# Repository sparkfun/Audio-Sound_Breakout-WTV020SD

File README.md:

**NOTE:** *This product has been retired from our catalog. For alternatives, try looking at the following products from the [Audio boards](https://www.sparkfun.com/categories/343):*

* [Little Soundie Audio Player](https://www.sparkfun.com/products/14006)
* [Qwiic MP3 Trigger](https://www.sparkfun.com/products/15165)

*If you are looking for more up-to-date info, please check out some of these resources to see how other users are still hacking and improving on this product.*

* *[SparkFun Forum](https://forum.sparkfun.com/)*
* *[IRC Channel](https://www.sparkfun.com/news/263)*

Audio-Sound Breakout
====================

[  
*Audio-Sound Breakout (WIG-11125)*](https://www.sparkfun.com/products/11125)

* Firmware was compiled in Arduino 1.0.3.
* Hardware was developed in EAGLE 6.3.0.
* Fritzing part created under 0.7.12.

License Information
-------------------
The hardware design is released under [CC-SA v3 license](http://creativecommons.org/licenses/by-sa/3.0/us/).

The firmware is released under a modified beerware license, allowing for the purchase of any libation, alcoholic or non.

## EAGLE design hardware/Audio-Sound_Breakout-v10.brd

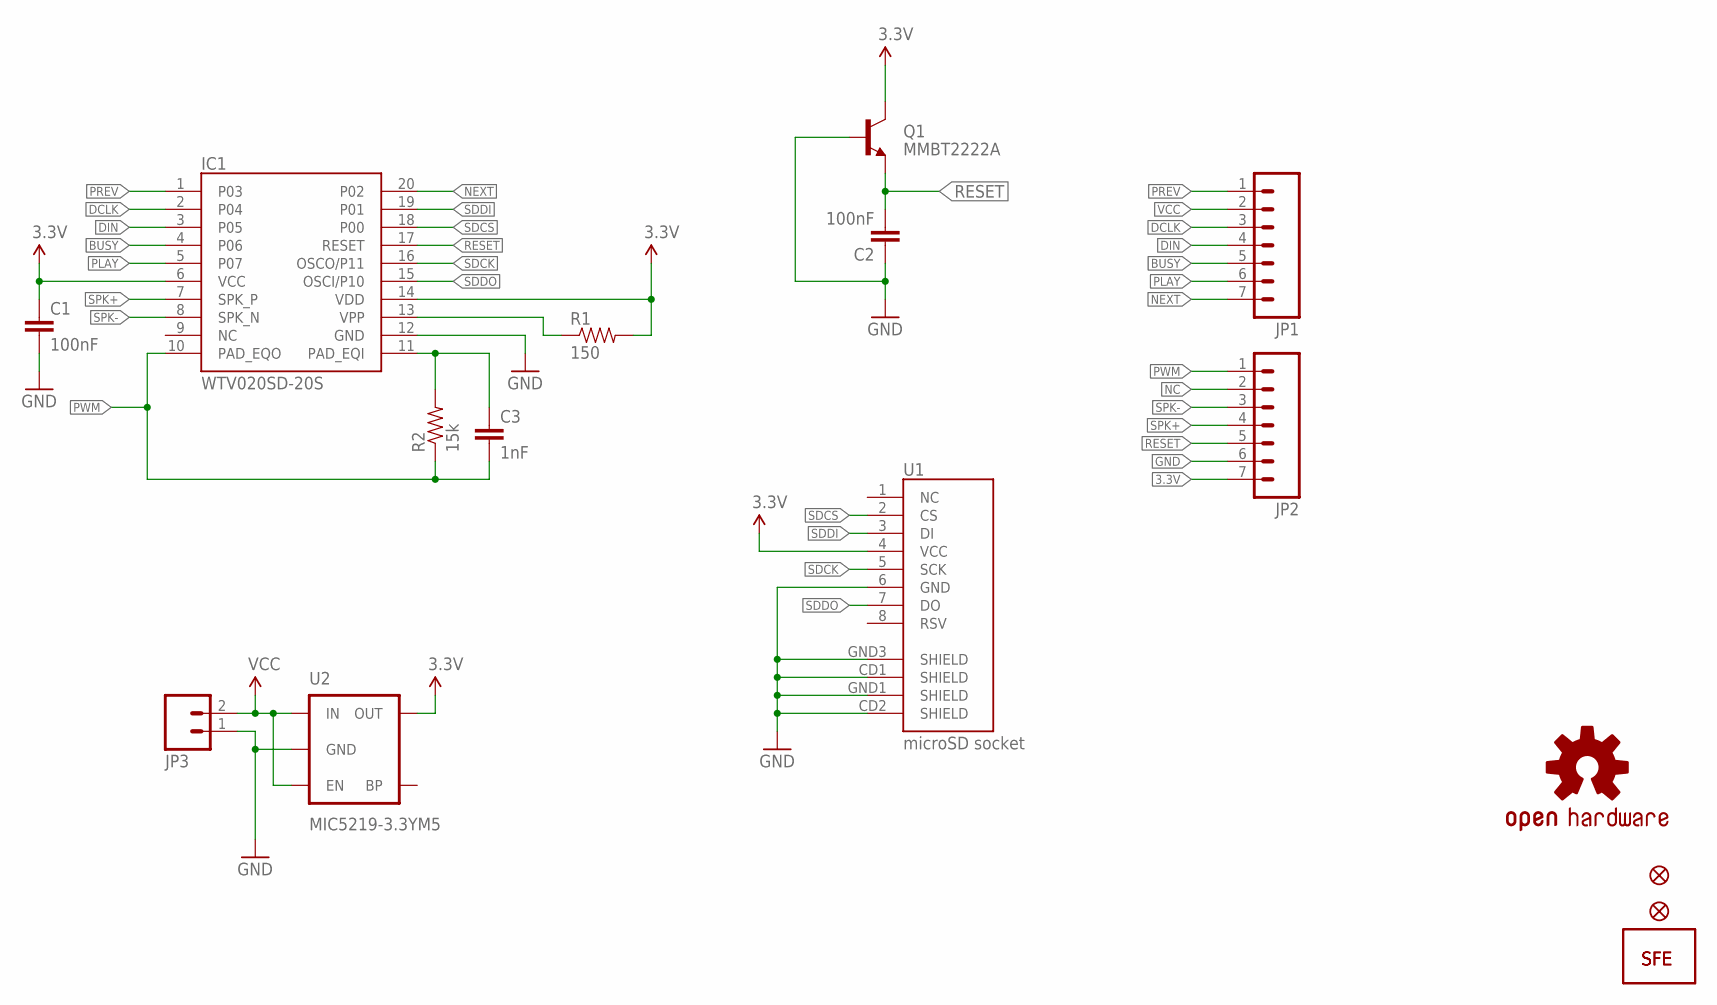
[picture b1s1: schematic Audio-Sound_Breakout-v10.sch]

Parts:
C1, C2: 100nF; 0402-CAP
C3: 1nF; 0402-CAP
IC1: WTV020SD-20S; SSOP_20
JP1, JP2: M07; 1X07
JP3: M02-JST-2MM-SMT; JST-2-SMD
JP4: LOGO-SFENW2; SFE-NEW-WEB
JP5: LOGO-SFENEW; SFE-NEW-WEBLOGO
JP6, JP7: FIDUCIALUFIDUCIAL; MICRO-FIDUCIAL
Q1: MMBT2222A; SOT23
R1: 150; 0402-RES
R2: 15k; 0402-RES
U1: microSD socket; MICRO-SD-SOCKET-PP
U2: MIC5219-3.3YM5; SOT23-5
U$1: OSHW-LOGOS; OSHW-LOGO-S

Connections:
3.3V: C1.1, IC1.6 (VCC), IC1.14 (VDD), JP2.7, Q1.3 (C), R1.2, U1.4 (VCC), U2.5 (OUT)
BUSY: IC1.4 (P06), JP1.5
DCLK: IC1.2 (P04), JP1.3
DIN: IC1.3 (P05), JP1.4
GND: C1.2, C2.1, IC1.12 (GND), JP2.6, JP3.1 (2), Q1.1 (B), U1.6 (GND), U1.CD1 (SHIELD), U1.CD2 (SHIELD), U1.GND1 (SHIELD), U1.GND3 (SHIELD), U2.2 (GND)
unnamed: IC1.13 (VPP), R1.1
unnamed: C3.1, IC1.11 (PAD_EQI), R2.2
NC: JP2.2
NEXT: IC1.20 (P02), JP1.7
PLAY: IC1.5 (P07), JP1.6
PREV: IC1.1 (P03), JP1.1
PWM: C3.2, IC1.10 (PAD_EQO), JP2.1, R2.1
RESET: C2.2, IC1.17 (RESET), JP2.5, Q1.2 (E)
SDCK: IC1.16 (OSCO/P11), U1.5 (SCK)
SDCS: IC1.18 (P00), U1.2 (CS)
SDDI: IC1.19 (P01), U1.3 (DI)
SDDO: IC1.15 (OSCI/P10), U1.7 (DO)
SPK+: IC1.7 (SPK_P), JP2.4
SPK-: IC1.8 (SPK_N), JP2.3
VCC: JP1.2, JP3.2 (1), U2.1 (IN), U2.3 (EN)

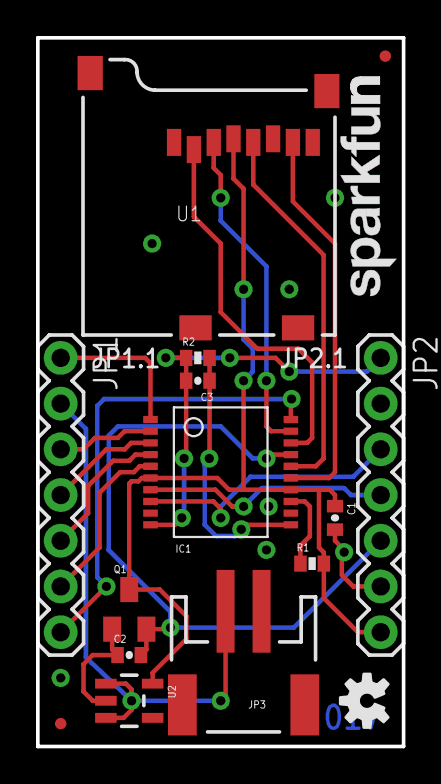
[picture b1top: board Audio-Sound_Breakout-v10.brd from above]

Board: 2 copper layers, 20.3 x 39.4 mm, 17 parts (1 on the bottom side), 19 nets.

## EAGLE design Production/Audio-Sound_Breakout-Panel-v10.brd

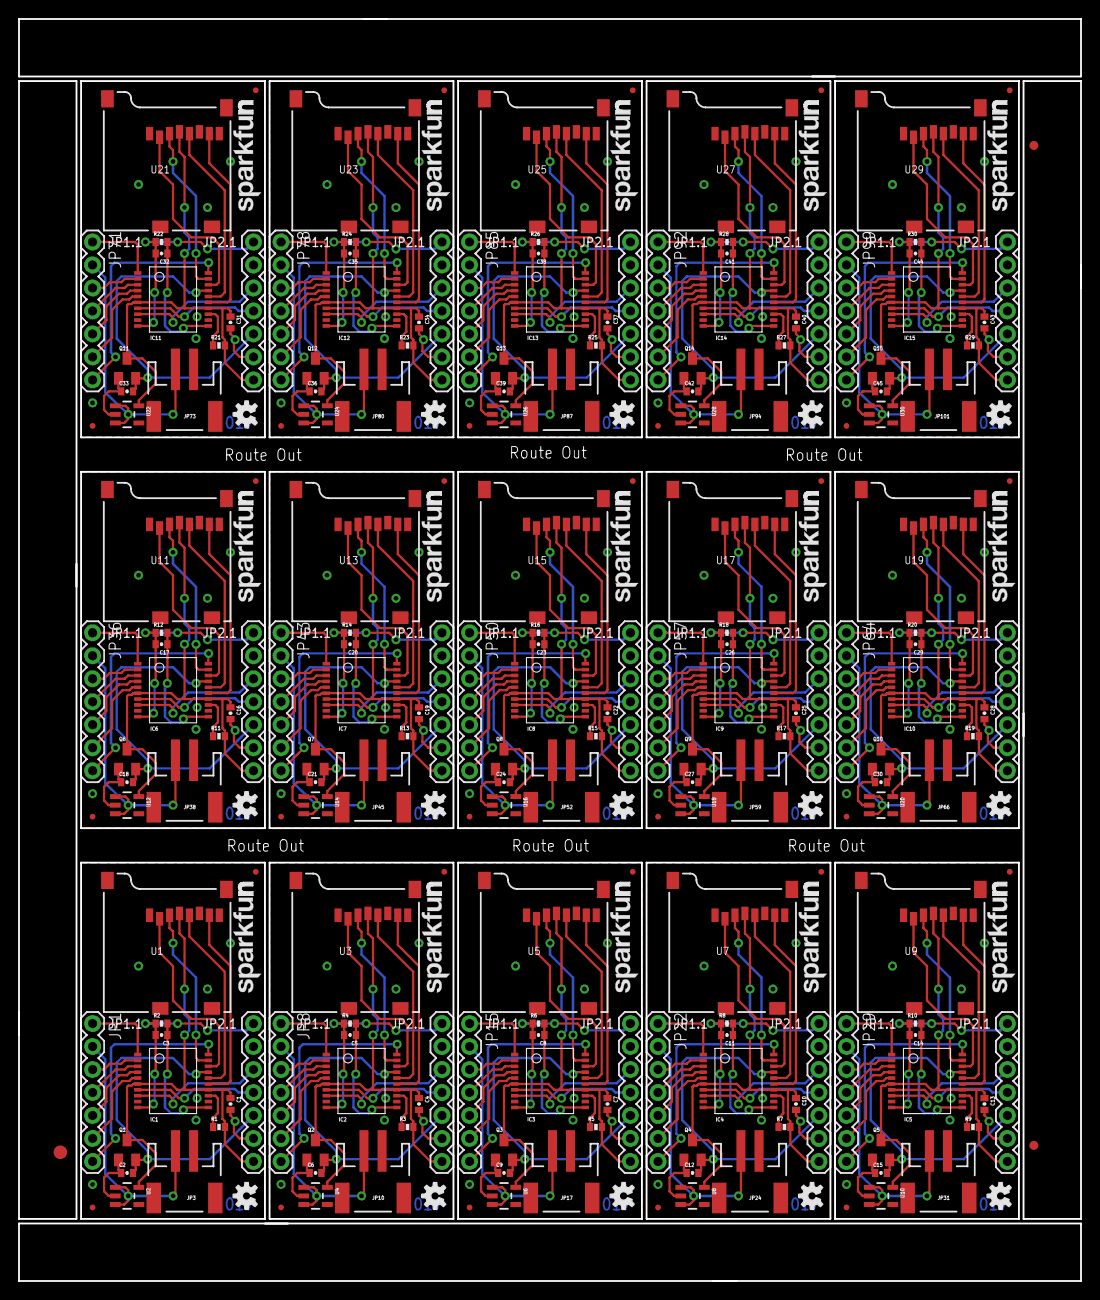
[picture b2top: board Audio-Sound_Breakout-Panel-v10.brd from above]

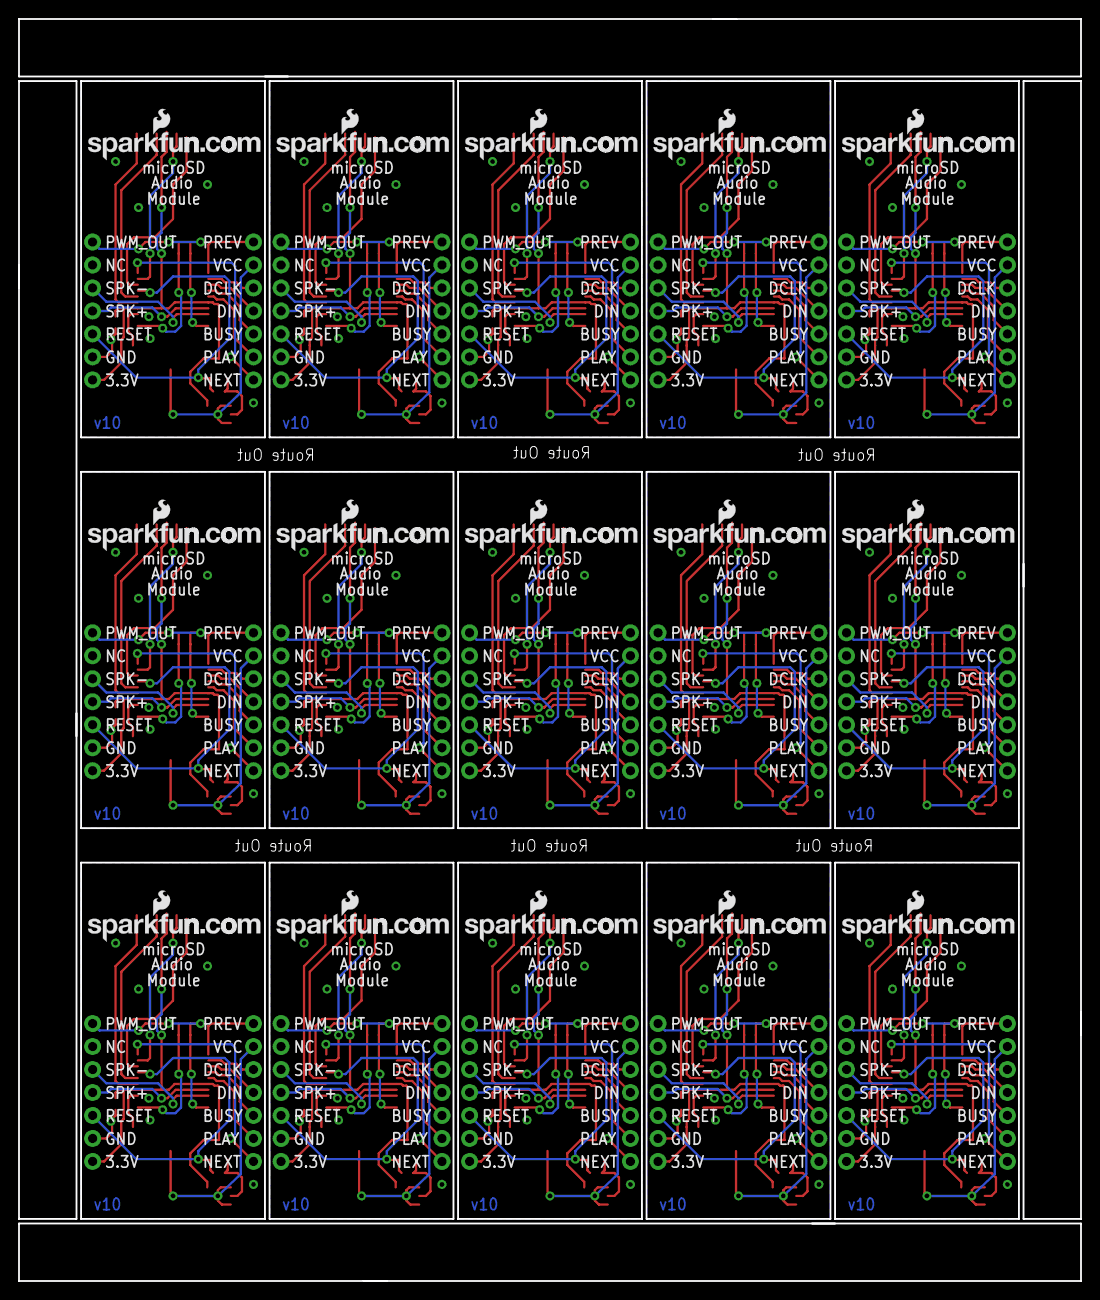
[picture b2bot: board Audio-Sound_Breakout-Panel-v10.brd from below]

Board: 2 copper layers, 117.3 x 139.4 mm, 258 parts (15 on the bottom side), 285 nets.

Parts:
C1, C2, C4, C6, C7, C9, C10, C12, C13, C15, C16, C18, C19, C21, C22, C24, C25, C27, C28, C30, C31, C33, C34, C36, C37, C39, C40, C42, C43, C45: 100nF; 0402-CAP
C3, C5, C8, C11, C14, C17, C20, C23, C26, C29, C32, C35, C38, C41, C44: 1nF; 0402-CAP
E$1: FIDUCIAL-1.5X3
E$7, E$8: FIDUCIAL-1X2
IC1, IC2, IC3, IC4, IC5, IC6, IC7, IC8, IC9, IC10, IC11, IC12, IC13, IC14, IC15: WTV020SD-20S; SSOP_20
JP1, JP2, JP8, JP9, JP15, JP16, JP22, JP23, JP29, JP30, JP36, JP37, JP43, JP44, JP50, JP51, JP57, JP58, JP64, JP65, JP71, JP72, JP78, JP79, JP85, JP86, JP92, JP93, JP99, JP100: 1X07
JP3, JP10, JP17, JP24, JP31, JP38, JP45, JP52, JP59, JP66, JP73, JP80, JP87, JP94, JP101: JST-2-SMD
JP4, JP11, JP18, JP25, JP32, JP39, JP46, JP53, JP60, JP67, JP74, JP81, JP88, JP95, JP102: LOGO-SFENW2; SFE-NEW-WEB
JP5, JP12, JP19, JP26, JP33, JP40, JP47, JP54, JP61, JP68, JP75, JP82, JP89, JP96, JP103: LOGO-SFENEW; SFE-NEW-WEBLOGO
JP6, JP7, JP13, JP14, JP20, JP21, JP27, JP28, JP34, JP35, JP41, JP42, JP48, JP49, JP55, JP56, JP62, JP63, JP69, JP70, JP76, JP77, JP83, JP84, JP90, JP91, JP97, JP98, JP104, JP105: FIDUCIALUFIDUCIAL; MICRO-FIDUCIAL
Q1, Q2, Q3, Q4, Q5, Q6, Q7, Q8, Q9, Q10, Q11, Q12, Q13, Q14, Q15: MMBT2222A; SOT23
R1, R3, R5, R7, R9, R11, R13, R15, R17, R19, R21, R23, R25, R27, R29: 150; 0402-RES
R2, R4, R6, R8, R10, R12, R14, R16, R18, R20, R22, R24, R26, R28, R30: 15k; 0402-RES
U1, U3, U5, U7, U9, U11, U13, U15, U17, U19, U21, U23, U25, U27, U29: microSD socket; MICRO-SD-SOCKET-PP
U2, U4, U6, U8, U10, U12, U14, U16, U18, U20, U22, U24, U26, U28, U30: MIC5219-3.3YM5; SOT23-5
U$1, U$2, U$3, U$4, U$5, U$6, U$7, U$8, U$9, U$10, U$11, U$12, U$13, U$14, U$15: OSHW-LOGOS; OSHW-LOGO-S

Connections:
3.3V: C1.1, IC1.6, IC1.14, JP2.7, Q1.3, R1.2, U1.4, U2.5
3.3V1: C4.1, IC2.6, IC2.14, JP9.7, Q2.3, R3.2, U3.4, U4.5
3.3V2: C7.1, IC3.6, IC3.14, JP16.7, Q3.3, R5.2, U5.4, U6.5
3.3V3: C10.1, IC4.6, IC4.14, JP23.7, Q4.3, R7.2, U7.4, U8.5
3.3V4: C13.1, IC5.6, IC5.14, JP30.7, Q5.3, R9.2, U9.4, U10.5
3.3V5: C16.1, IC6.6, IC6.14, JP37.7, Q6.3, R11.2, U11.4, U12.5
3.3V6: C19.1, IC7.6, IC7.14, JP44.7, Q7.3, R13.2, U13.4, U14.5
3.3V7: C22.1, IC8.6, IC8.14, JP51.7, Q8.3, R15.2, U15.4, U16.5
3.3V8: C25.1, IC9.6, IC9.14, JP58.7, Q9.3, R17.2, U17.4, U18.5
3.3V9: C28.1, IC10.6, IC10.14, JP65.7, Q10.3, R19.2, U19.4, U20.5
3.3V10: C31.1, IC11.6, IC11.14, JP72.7, Q11.3, R21.2, U21.4, U22.5
3.3V11: C34.1, IC12.6, IC12.14, JP79.7, Q12.3, R23.2, U23.4, U24.5
3.3V12: C37.1, IC13.6, IC13.14, JP86.7, Q13.3, R25.2, U25.4, U26.5
3.3V13: C40.1, IC14.6, IC14.14, JP93.7, Q14.3, R27.2, U27.4, U28.5
3.3V14: C43.1, IC15.6, IC15.14, JP100.7, Q15.3, R29.2, U29.4, U30.5
BUSY: IC1.4, JP1.5
BUSY1: IC2.4, JP8.5
BUSY2: IC3.4, JP15.5
BUSY3: IC4.4, JP22.5
BUSY4: IC5.4, JP29.5
BUSY5: IC6.4, JP36.5
BUSY6: IC7.4, JP43.5
BUSY7: IC8.4, JP50.5
BUSY8: IC9.4, JP57.5
BUSY9: IC10.4, JP64.5
BUSY10: IC11.4, JP71.5
BUSY11: IC12.4, JP78.5
BUSY12: IC13.4, JP85.5
BUSY13: IC14.4, JP92.5
BUSY14: IC15.4, JP99.5
DCLK: IC1.2, JP1.3
DCLK1: IC2.2, JP8.3
DCLK2: IC3.2, JP15.3
DCLK3: IC4.2, JP22.3
DCLK4: IC5.2, JP29.3
DCLK5: IC6.2, JP36.3
DCLK6: IC7.2, JP43.3
DCLK7: IC8.2, JP50.3
DCLK8: IC9.2, JP57.3
DCLK9: IC10.2, JP64.3
DCLK10: IC11.2, JP71.3
DCLK11: IC12.2, JP78.3
DCLK12: IC13.2, JP85.3
DCLK13: IC14.2, JP92.3
DCLK14: IC15.2, JP99.3
DIN: IC1.3, JP1.4
DIN1: IC2.3, JP8.4
DIN2: IC3.3, JP15.4
DIN3: IC4.3, JP22.4
DIN4: IC5.3, JP29.4
DIN5: IC6.3, JP36.4
DIN6: IC7.3, JP43.4
DIN7: IC8.3, JP50.4
DIN8: IC9.3, JP57.4
DIN9: IC10.3, JP64.4
DIN10: IC11.3, JP71.4
DIN11: IC12.3, JP78.4
DIN12: IC13.3, JP85.4
DIN13: IC14.3, JP92.4
DIN14: IC15.3, JP99.4
GND: C1.2, C2.1, IC1.12, JP2.6, JP3.1, Q1.1, U1.6, U1.CD1, U1.CD2, U1.GND1, U1.GND3, U2.2
GND1: C4.2, C6.1, IC2.12, JP9.6, JP10.1, Q2.1, U3.6, U3.CD1, U3.CD2, U3.GND1, U3.GND3, U4.2
GND2: C7.2, C9.1, IC3.12, JP16.6, JP17.1, Q3.1, U5.6, U5.CD1, U5.CD2, U5.GND1, U5.GND3, U6.2
GND3: C10.2, C12.1, IC4.12, JP23.6, JP24.1, Q4.1, U7.6, U7.CD1, U7.CD2, U7.GND1, U7.GND3, U8.2
GND4: C13.2, C15.1, IC5.12, JP30.6, JP31.1, Q5.1, U9.6, U9.CD1, U9.CD2, U9.GND1, U9.GND3, U10.2
GND5: C16.2, C18.1, IC6.12, JP37.6, JP38.1, Q6.1, U11.6, U11.CD1, U11.CD2, U11.GND1, U11.GND3, U12.2
GND6: C19.2, C21.1, IC7.12, JP44.6, JP45.1, Q7.1, U13.6, U13.CD1, U13.CD2, U13.GND1, U13.GND3, U14.2
GND7: C22.2, C24.1, IC8.12, JP51.6, JP52.1, Q8.1, U15.6, U15.CD1, U15.CD2, U15.GND1, U15.GND3, U16.2
GND8: C25.2, C27.1, IC9.12, JP58.6, JP59.1, Q9.1, U17.6, U17.CD1, U17.CD2, U17.GND1, U17.GND3, U18.2
GND9: C28.2, C30.1, IC10.12, JP65.6, JP66.1, Q10.1, U19.6, U19.CD1, U19.CD2, U19.GND1, U19.GND3, U20.2
GND10: C31.2, C33.1, IC11.12, JP72.6, JP73.1, Q11.1, U21.6, U21.CD1, U21.CD2, U21.GND1, U21.GND3, U22.2
GND11: C34.2, C36.1, IC12.12, JP79.6, JP80.1, Q12.1, U23.6, U23.CD1, U23.CD2, U23.GND1, U23.GND3, U24.2
GND12: C37.2, C39.1, IC13.12, JP86.6, JP87.1, Q13.1, U25.6, U25.CD1, U25.CD2, U25.GND1, U25.GND3, U26.2
GND13: C40.2, C42.1, IC14.12, JP93.6, JP94.1, Q14.1, U27.6, U27.CD1, U27.CD2, U27.GND1, U27.GND3, U28.2
GND14: C43.2, C45.1, IC15.12, JP100.6, JP101.1, Q15.1, U29.6, U29.CD1, U29.CD2, U29.GND1, U29.GND3, U30.2
unnamed: IC1.13, R1.1
unnamed: C3.1, IC1.11, R2.2
unnamed: IC2.13, R3.1
unnamed: C5.1, IC2.11, R4.2
unnamed: IC3.13, R5.1
unnamed: C8.1, IC3.11, R6.2
unnamed: IC4.13, R7.1
unnamed: C11.1, IC4.11, R8.2
unnamed: IC5.13, R9.1
unnamed: C14.1, IC5.11, R10.2
unnamed: IC6.13, R11.1
unnamed: C17.1, IC6.11, R12.2
unnamed: IC7.13, R13.1
unnamed: C20.1, IC7.11, R14.2
unnamed: IC8.13, R15.1
unnamed: C23.1, IC8.11, R16.2
unnamed: IC9.13, R17.1
unnamed: C26.1, IC9.11, R18.2
unnamed: IC10.13, R19.1
unnamed: C29.1, IC10.11, R20.2
unnamed: IC11.13, R21.1
unnamed: C32.1, IC11.11, R22.2
unnamed: IC12.13, R23.1
unnamed: C35.1, IC12.11, R24.2
unnamed: IC13.13, R25.1
unnamed: C38.1, IC13.11, R26.2
unnamed: IC14.13, R27.1
unnamed: C41.1, IC14.11, R28.2
unnamed: IC15.13, R29.1
unnamed: C44.1, IC15.11, R30.2
NEXT: IC1.20, JP1.7
NEXT1: IC2.20, JP8.7
NEXT2: IC3.20, JP15.7
NEXT3: IC4.20, JP22.7
NEXT4: IC5.20, JP29.7
NEXT5: IC6.20, JP36.7
NEXT6: IC7.20, JP43.7
NEXT7: IC8.20, JP50.7
NEXT8: IC9.20, JP57.7
NEXT9: IC10.20, JP64.7
NEXT10: IC11.20, JP71.7
NEXT11: IC12.20, JP78.7
NEXT12: IC13.20, JP85.7
NEXT13: IC14.20, JP92.7
NEXT14: IC15.20, JP99.7
PLAY: IC1.5, JP1.6
PLAY1: IC2.5, JP8.6
PLAY2: IC3.5, JP15.6
PLAY3: IC4.5, JP22.6
PLAY4: IC5.5, JP29.6
PLAY5: IC6.5, JP36.6
PLAY6: IC7.5, JP43.6
PLAY7: IC8.5, JP50.6
PLAY8: IC9.5, JP57.6
PLAY9: IC10.5, JP64.6
PLAY10: IC11.5, JP71.6
PLAY11: IC12.5, JP78.6
PLAY12: IC13.5, JP85.6
PLAY13: IC14.5, JP92.6
PLAY14: IC15.5, JP99.6
PREV: IC1.1, JP1.1
PREV1: IC2.1, JP8.1
PREV2: IC3.1, JP15.1
PREV3: IC4.1, JP22.1
PREV4: IC5.1, JP29.1
PREV5: IC6.1, JP36.1
PREV6: IC7.1, JP43.1
PREV7: IC8.1, JP50.1
PREV8: IC9.1, JP57.1
PREV9: IC10.1, JP64.1
PREV10: IC11.1, JP71.1
PREV11: IC12.1, JP78.1
PREV12: IC13.1, JP85.1
PREV13: IC14.1, JP92.1
PREV14: IC15.1, JP99.1
PWM: C3.2, IC1.10, JP2.1, R2.1
PWM1: C5.2, IC2.10, JP9.1, R4.1
PWM2: C8.2, IC3.10, JP16.1, R6.1
PWM3: C11.2, IC4.10, JP23.1, R8.1
PWM4: C14.2, IC5.10, JP30.1, R10.1
PWM5: C17.2, IC6.10, JP37.1, R12.1
PWM6: C20.2, IC7.10, JP44.1, R14.1
PWM7: C23.2, IC8.10, JP51.1, R16.1
PWM8: C26.2, IC9.10, JP58.1, R18.1
PWM9: C29.2, IC10.10, JP65.1, R20.1
PWM10: C32.2, IC11.10, JP72.1, R22.1
PWM11: C35.2, IC12.10, JP79.1, R24.1
PWM12: C38.2, IC13.10, JP86.1, R26.1
PWM13: C41.2, IC14.10, JP93.1, R28.1
PWM14: C44.2, IC15.10, JP100.1, R30.1
RESET: C2.2, IC1.17, JP2.5, Q1.2
RESET1: C6.2, IC2.17, JP9.5, Q2.2
RESET2: C9.2, IC3.17, JP16.5, Q3.2
RESET3: C12.2, IC4.17, JP23.5, Q4.2
RESET4: C15.2, IC5.17, JP30.5, Q5.2
RESET5: C18.2, IC6.17, JP37.5, Q6.2
RESET6: C21.2, IC7.17, JP44.5, Q7.2
RESET7: C24.2, IC8.17, JP51.5, Q8.2
RESET8: C27.2, IC9.17, JP58.5, Q9.2
RESET9: C30.2, IC10.17, JP65.5, Q10.2
RESET10: C33.2, IC11.17, JP72.5, Q11.2
RESET11: C36.2, IC12.17, JP79.5, Q12.2
RESET12: C39.2, IC13.17, JP86.5, Q13.2
RESET13: C42.2, IC14.17, JP93.5, Q14.2
RESET14: C45.2, IC15.17, JP100.5, Q15.2
SDCK: IC1.16, U1.5
SDCK1: IC2.16, U3.5
SDCK2: IC3.16, U5.5
SDCK3: IC4.16, U7.5
SDCK4: IC5.16, U9.5
SDCK5: IC6.16, U11.5
SDCK6: IC7.16, U13.5
SDCK7: IC8.16, U15.5
SDCK8: IC9.16, U17.5
SDCK9: IC10.16, U19.5
SDCK10: IC11.16, U21.5
SDCK11: IC12.16, U23.5
SDCK12: IC13.16, U25.5
SDCK13: IC14.16, U27.5
SDCK14: IC15.16, U29.5
SDCS: IC1.18, U1.2
SDCS1: IC2.18, U3.2
SDCS2: IC3.18, U5.2
SDCS3: IC4.18, U7.2
SDCS4: IC5.18, U9.2
SDCS5: IC6.18, U11.2
SDCS6: IC7.18, U13.2
SDCS7: IC8.18, U15.2
SDCS8: IC9.18, U17.2
SDCS9: IC10.18, U19.2
SDCS10: IC11.18, U21.2
SDCS11: IC12.18, U23.2
SDCS12: IC13.18, U25.2
SDCS13: IC14.18, U27.2
SDCS14: IC15.18, U29.2
SDDI: IC1.19, U1.3
SDDI1: IC2.19, U3.3
SDDI2: IC3.19, U5.3
SDDI3: IC4.19, U7.3
SDDI4: IC5.19, U9.3
SDDI5: IC6.19, U11.3
SDDI6: IC7.19, U13.3
SDDI7: IC8.19, U15.3
SDDI8: IC9.19, U17.3
SDDI9: IC10.19, U19.3
SDDI10: IC11.19, U21.3
SDDI11: IC12.19, U23.3
SDDI12: IC13.19, U25.3
SDDI13: IC14.19, U27.3
SDDI14: IC15.19, U29.3
SDDO: IC1.15, U1.7
SDDO1: IC2.15, U3.7
SDDO2: IC3.15, U5.7
SDDO3: IC4.15, U7.7
SDDO4: IC5.15, U9.7
SDDO5: IC6.15, U11.7
SDDO6: IC7.15, U13.7
SDDO7: IC8.15, U15.7
SDDO8: IC9.15, U17.7
SDDO9: IC10.15, U19.7
SDDO10: IC11.15, U21.7
SDDO11: IC12.15, U23.7
SDDO12: IC13.15, U25.7
SDDO13: IC14.15, U27.7
SDDO14: IC15.15, U29.7
SPK+: IC1.7, JP2.4
SPK+1: IC2.7, JP9.4
SPK+2: IC3.7, JP16.4
SPK+3: IC4.7, JP23.4
SPK+4: IC5.7, JP30.4
SPK+5: IC6.7, JP37.4
SPK+6: IC7.7, JP44.4
SPK+7: IC8.7, JP51.4
SPK+8: IC9.7, JP58.4
SPK+9: IC10.7, JP65.4
SPK+10: IC11.7, JP72.4
SPK+11: IC12.7, JP79.4
SPK+12: IC13.7, JP86.4
SPK+13: IC14.7, JP93.4
SPK+14: IC15.7, JP100.4
SPK-: IC1.8, JP2.3
SPK-1: IC2.8, JP9.3
SPK-2: IC3.8, JP16.3
SPK-3: IC4.8, JP23.3
SPK-4: IC5.8, JP30.3
SPK-5: IC6.8, JP37.3
SPK-6: IC7.8, JP44.3
SPK-7: IC8.8, JP51.3
SPK-8: IC9.8, JP58.3
SPK-9: IC10.8, JP65.3
SPK-10: IC11.8, JP72.3
SPK-11: IC12.8, JP79.3
SPK-12: IC13.8, JP86.3
SPK-13: IC14.8, JP93.3
SPK-14: IC15.8, JP100.3
VCC: JP1.2, JP3.2, U2.1, U2.3
VCC1: JP8.2, JP10.2, U4.1, U4.3
VCC2: JP15.2, JP17.2, U6.1, U6.3
VCC3: JP22.2, JP24.2, U8.1, U8.3
VCC4: JP29.2, JP31.2, U10.1, U10.3
VCC5: JP36.2, JP38.2, U12.1, U12.3
VCC6: JP43.2, JP45.2, U14.1, U14.3
VCC7: JP50.2, JP52.2, U16.1, U16.3
VCC8: JP57.2, JP59.2, U18.1, U18.3
VCC9: JP64.2, JP66.2, U20.1, U20.3
VCC10: JP71.2, JP73.2, U22.1, U22.3
VCC11: JP78.2, JP80.2, U24.1, U24.3
VCC12: JP85.2, JP87.2, U26.1, U26.3
VCC13: JP92.2, JP94.2, U28.1, U28.3
VCC14: JP99.2, JP101.2, U30.1, U30.3

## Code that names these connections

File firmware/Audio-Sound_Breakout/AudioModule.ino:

//-----------------------------------------------------------------------------
// Pin definitions
#define RESET 9    // Pull this low for at least 6ms to reset the audio module. 
                   //  Allow at least 300ms after reset before interacting with
                   //  the chip.
#define NEXT  8    // Play the next track. If you wish to advance the pointer
                   //  but not play the next track, you must immediately follow
                   //  a toggle of this pin with a toggle of the PLAY pin. Note
                   //  that the pointer for pin operations is different to the
                   //  pointer for the 2-wire serial controller. See above for
                   //  more instructions.
#define PREV  7    // Just like NEXT, but backwards.
#define PLAY  6    // Play, or stop, the current track. This stops playback, so
                   //  upon the next toggle of the PLAY pin, playback will
                   //  begin from the start of the current track. It does NOT
                   //  pause playback.
#define BUSY  5    // HIGH during playback.
#define DOUT  4    // Data input from a microcontroller.
#define DCLK  3    // Data clock from a microcontroller.

// Opcode definitions- the 2-wire serial (which is NOT I2C- it is close to SPI
//  without a CS or MISO, but the Arduino can't clock data slowly enough to
//  suit the widget when using the internal SPI peripheral).
#define OPCODE_PLAY_PAUSE  0xFFFE   // Play a track, or pause the current
                                    //  playback. Note that this requires that
                                    //  you first send a number from 0-511 to
                                    //  the module to indicate which track you
                                    //  wish to play back- simply sending the
                                    //  PLAY_PAUSE opcode has no effect other
                                    //  than pausing playback.
#define OPCODE_STOP        0xFFFF   // Stops the current playback. Subsequent
                                    //  toggling of the PLAY pin will start
                                    //  playback as though no previous track
                                    //  were playing.
#define OPCODE_VOL         0xFFF0   // Set the volume. 0xFFF0 is muted, 0xFFF7
                                    //  is max. Defaults to max on startup.

byte file = 0;   // This is a file counter used to internally track the pointer
                 //  for playback. There is no way to read the internal pointer
                 //  and find out which track will play if you simply strobe the
                 //  PLAY pin, or which track you'll be moving to if you strobe
                 //  NEXT or PREV.

void setup()
{
  Serial.begin(57600);
  pinSetup();
  resetModule();
}

void loop() 
{
  if (Serial.available() > 0)
  {
    byte command = Serial.read();
    switch(command)
    {
      case 'p':
        sendCommand((unsigned int) file);
        sendCommand(OPCODE_PLAY_PAUSE);
        break;
      case 's':
        sendCommand(OPCODE_STOP);
        break;
      case 'n':
        if (file++ == 11) file = 0;
        digitalWrite(NEXT, LOW);
        delay(10);
        digitalWrite(NEXT, HIGH);
        break;
      case 'b':
        if (file-- == 255) file = 10;
        digitalWrite(PREV, LOW);
        delay(10);
        digitalWrite(PREV, HIGH);
        break;
      case '+':
        if (file++ == 11) file = 0;
        digitalWrite(NEXT, LOW);
        delay(10);
        digitalWrite(NEXT, HIGH);
        while(digitalRead(BUSY) == HIGH);
        digitalWrite(PLAY, LOW);
        delay(10);
        digitalWrite(PLAY, HIGH);
        break;
      case '-':
        if (file-- == 255) file = 10;
        digitalWrite(PREV, LOW);
        delay(10);
        digitalWrite(PREV, HIGH);
        while(digitalRead(BUSY) == HIGH);
        digitalWrite(PLAY, LOW);
        delay(10);
        digitalWrite(PLAY, HIGH);
        break;
      case 't':
        digitalWrite(PLAY, LOW);
        delay(10);
        digitalWrite(PLAY, HIGH);
        break;
      case 'x':
        sendCommand(OPCODE_PLAY_PAUSE);
        break;
    } 
  }
}

void pinSetup()
{
  pinMode(RESET, OUTPUT);
  digitalWrite(RESET, LOW);
  pinMode(NEXT, OUTPUT);
  digitalWrite(NEXT, HIGH);
  pinMode(PREV, OUTPUT);
  digitalWrite(PREV, HIGH);
  pinMode(PLAY, OUTPUT);
  digitalWrite(PLAY, HIGH);
  
  pinMode(DOUT, OUTPUT);
  digitalWrite(DOUT, HIGH);
  pinMode(DCLK, OUTPUT);
  digitalWrite(DOUT, HIGH);
  
  pinMode(BUSY, INPUT);
}

void resetModule()
{
  digitalWrite(RESET, LOW);
  delay(100);
  digitalWrite(RESET, HIGH);
  delay(500);
}

void sendCommand(unsigned int command)
{
  digitalWrite(DCLK, LOW);
  delayMicroseconds(1900);
  for (byte i = 0; i < 16; i++)
  {
    delayMicroseconds(100);
    digitalWrite(DCLK, LOW);
    digitalWrite(DOUT, LOW);
    if ((command & 0x8000) != 0)
    {
      digitalWrite(DOUT, HIGH);
    }
    delayMicroseconds(100);
    digitalWrite(DCLK, HIGH);
    command = command<<1;
  }
}
      
    

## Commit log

2013-04-16 Initial commit of production files.
2015-10-23 recreated panel v10

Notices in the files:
parts and their libraries:
SparkFun-DigitalIC: Licensing: CC v3.0 Share-Alike You are welcome to use this library for commercial purposes.
SparkFun-Retired: Licensing:Creative Commons ShareAlike 4.0 International - https://creativecommons.org/licenses/by-sa/4.0
SparkFun-Aesthetics: Released under the Creative Commons
